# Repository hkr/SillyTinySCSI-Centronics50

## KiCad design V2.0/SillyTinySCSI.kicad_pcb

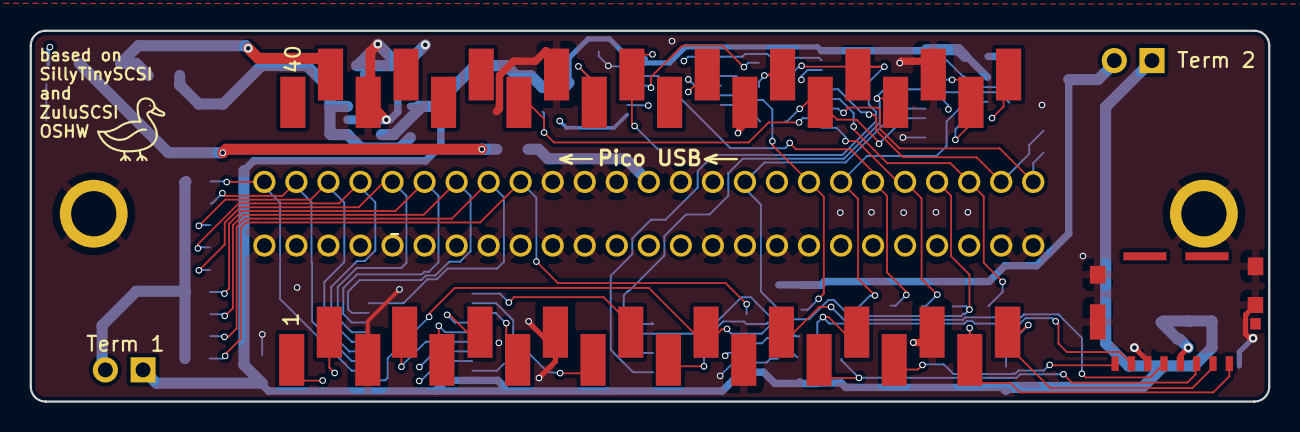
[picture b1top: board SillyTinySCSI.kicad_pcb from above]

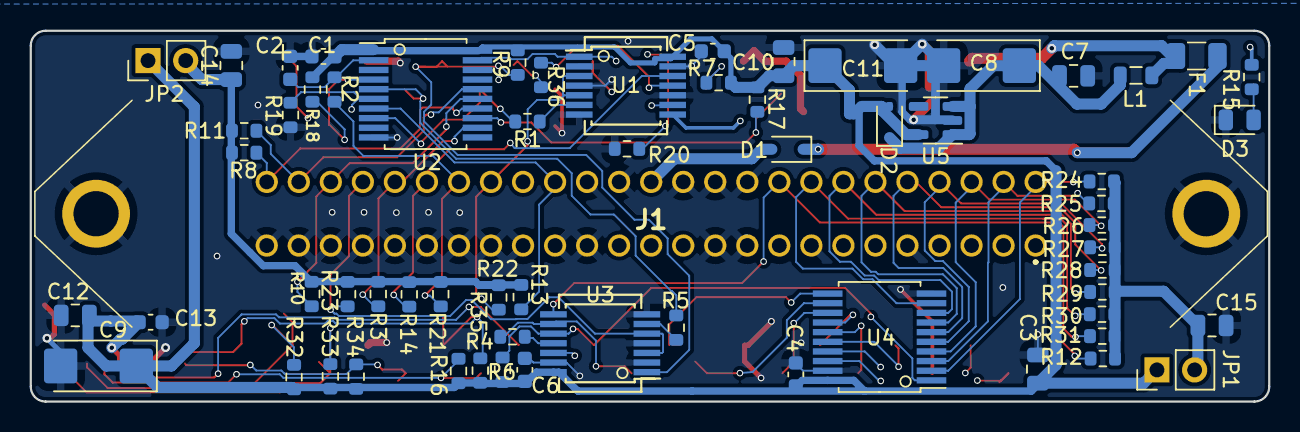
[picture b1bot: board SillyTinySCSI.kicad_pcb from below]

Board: 4 copper layers, 83.5 x 25.0 mm, 66 parts (64 on the bottom side), 59 nets.

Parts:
C1, C4, C5, C6, C13: 100nF; C_0603_1608Metric
C2: 12pF; C_0603_1608Metric
C3, C7, C10, C12, C14, C15: 10uF; C_0805_2012Metric
C8, C9, C11: 220uF; CP_EIA-6032-15_Kemet-U_Pad2.25x2.35mm_HandSolder
D1, D2: D_Schottky; D_SOD-323
D3: LED; LED_0805_2012Metric
F1: 500mA Hold; Fuse_1206_3216Metric
J1: Centronics50_Plug; 111050113L001
J2: Micro_SD_Card_Det1; microsd_molex_1051620001
JP1: Term 1; PinHeader_1x02_P2.54mm_Vertical
JP2: Term 2; PinHeader_1x02_P2.54mm_Vertical
L1: Ferrite_Bead_Small; L_0805_2012Metric
R1, R4, R5, R20: 1k; R_0603_1608Metric
R2, R3, R8, R10, R11, R12, R13, R14, R21, R22, R23, R24, R25, R26, R27, R28, R29, R30, R31: 110; R_0603_1608Metric
R6, R7, R9, R16, R17, R18, R19, R32, R33, R34, R35, R36: 4k7; R_0603_1608Metric
R15: 51; R_0603_1608Metric
U1, U3: 74LVT125; SSOP_TSSOP-14_4.4x5mm_Pitch0.65mm_PCBWay-MaskClearance0.22mm
U2, U4: 74LVT245; SSOP_TSSOP-20_5.3x7.2mm_P0.65mm
U5: TLV75728PDBVR; SOT-23-5
U6: Pico W; RPi_Pico_W_SMD headers

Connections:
+2V8: C1.1, C3.1, C4.1, C5.1, C6.2, C9.1, C10.1, C11.1, C12.2, C13.2, D2.2 (A), J2.4 (VDD), JP1.1 (A), JP2.1 (A), R6.1, R7.1, R9.1, R16.2, R17.1, R18.1, R32.2, R33.2, R34.2, R35.2, U1.14 (VCC), U2.1 (A->B), U2.20 (VCC), U3.14 (VCC), U4.20 (VCC), U5.5 (OUT)
+5VP: F1.2, L1.2, U6.39 (VSYS)
/cpu/LED_SWO: U1.9, U6.21 (GPIO16)
/cpu/SDIO_CLK: J2.5 (CLK), U6.14 (GPIO10)
/cpu/SDIO_CMD: J2.3 (CMD), R16.1, U6.15 (GPIO11)
/cpu/SDIO_D0: J2.7 (DAT0), R35.1, U6.16 (GPIO12)
/cpu/SDIO_D1: J2.8 (DAT1), R34.1, U6.17 (GPIO13)
/cpu/SDIO_D2: J2.1 (DAT2), R33.1, U6.19 (GPIO14)
/cpu/SDIO_D3: J2.2 (DAT3/CD), R32.1, U6.20 (GPIO15)
/power/5V_REG: C7.1, C8.1, D2.1 (K), L1.1, U5.1 (IN), U5.3 (EN)
GND: C1.2, C2.2, C3.2, C4.2, C5.2, C6.1, C7.2, C8.2, C9.2, C10.2, C11.2, C12.1, C13.1, C14.2, C15.2, D3.1 (K), J1.1, J1.2, J1.3, J1.4, J1.5, J1.6, J1.7, J1.8, J1.9, J1.10, J1.11, J1.15, J1.16, J1.17, J1.18, J1.19, J1.20, J1.21, J1.22, J1.23, J1.24, J1.25, J1.35, J1.36, J1.37, J1.39, J1.40, J1.MH1, J1.MH2, J2.6 (VSS), J2.10 (SHIELD), R19.1, R20.2, U1.2, U1.4, U1.7 (GND), U1.10, U1.13, U2.10 (GND), U3.2, U3.4, U3.7 (GND), U3.13, U4.10 (GND), U4.19 (CE), U5.2 (GND), U6.3 (GND), U6.8 (GND), U6.13 (GND), U6.18 (GND), U6.23 (GND), U6.28 (GND), U6.33 (AGND), U6.38 (GND)
unnamed: D1.1 (K), F1.1
unnamed: D3.2 (A), R15.1
unnamed: C15.1, JP1.2 (B), R12.2, R24.2, R25.2, R26.2, R27.2, R28.2, R29.2, R30.2, R31.2
unnamed: C14.1, JP2.2 (B), R3.2, R8.2, R10.2, R11.2, R13.2, R14.2, R21.2, R22.2, R23.2
unnamed: R1.2, U1.6
unnamed: R4.1, U3.11
unnamed: R5.2, U3.6
unnamed: R15.2, U1.8
unnamed: R36.1, U6.27 (GPIO21)
TERMPWR_5V: D1.2 (A), J1.38
~DATA_DIR: R6.2, U3.10, U4.1 (A->B), U6.12 (GPIO9)
~DBGLOG: R18.2, U2.4 (A2), U6.22 (GPIO17)
~GPIO_ACK: R20.1, U2.18 (B0), U6.31 (GPIO26_ADC0)
~GPIO_ATN: R17.2, U2.13 (B5), U6.34 (GPIO28_ADC2)
~GPIO_CD_SEL: R5.1, U2.5 (A3), U6.24 (GPIO18)
~GPIO_DB0: U4.18 (B0), U6.1 (GPIO0)
~GPIO_DB1: U4.17 (B1), U6.2 (GPIO1)
~GPIO_DB2: U4.16 (B2), U6.4 (GPIO2)
~GPIO_DB3: U4.15 (B3), U6.5 (GPIO3)
~GPIO_DB4: U4.14 (B4), U6.6 (GPIO4)
~GPIO_DB5: U4.13 (B5), U6.7 (GPIO5)
~GPIO_DB6: U4.12 (B6), U6.9 (GPIO6)
~GPIO_DB7: U4.11 (B7), U6.10 (GPIO7)
~GPIO_DBP: R4.2, U3.9, U6.11 (GPIO8)
~GPIO_IO: R19.2, U2.6 (A4), U6.29 (GPIO22)
~GPIO_MSG_BSY: R1.1, U2.8 (A6), U6.26 (GPIO20)
~IN_RST: R36.2, U1.11
~OUT_BSY: R7.2, U1.1, U2.19 (CE), U6.32 (GPIO27_ADC1)
~OUT_SEL: R9.2, U3.1, U6.25 (GPIO19)
~RC_ACK: C2.1, R2.2, U2.2 (A0)
~SCSI_ACK: J1.44, R2.1, R21.1
~SCSI_ATN: J1.41, R13.1, U2.7 (A5)
~SCSI_BSY: J1.43, R22.1, U1.3, U1.5
~SCSI_CD: J1.48, R10.1, U2.15 (B3)
~SCSI_DB0: J1.26, R24.1, U4.2 (A0)
~SCSI_DB1: J1.27, R25.1, U4.3 (A1)
~SCSI_DB2: J1.28, R26.1, U4.4 (A2)
~SCSI_DB3: J1.29, R27.1, U4.5 (A3)
~SCSI_DB4: J1.30, R28.1, U4.6 (A4)
~SCSI_DB5: J1.31, R29.1, U4.7 (A5)
~SCSI_DB6: J1.32, R30.1, U4.8 (A6)
~SCSI_DB7: J1.33, R31.1, U4.9 (A7)
~SCSI_DBP: J1.34, R12.1, U3.8, U3.12
~SCSI_IO: J1.50, R8.1, U2.14 (B4)
~SCSI_MSG: J1.46, R3.1, U2.12 (B6)
~SCSI_REQ: J1.49, R11.1, U2.16 (B2)
~SCSI_RST: J1.45, R14.1, U1.12
~SCSI_SEL: J1.47, R23.1, U3.3, U3.5

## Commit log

2024-02-02 Initial version of Centronics 50 SillyTinySCSI

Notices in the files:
parts and their libraries:
License: Licensed under CERN Open Hardware License Strongly Reciprocal Version 2
LicenseURL: https://spdx.org/licenses/CERN-OHL-S-2.0.html
